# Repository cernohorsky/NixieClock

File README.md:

# NixieClock Arduino Mega shield
NixieClock PCB for nixie tubes ZM1080, ZM1082, Z570M, Z5700M. High voltage DC-DC convertor. RTC for time synchronization.

<b>Ideas:</b><br>
Different DCDC convertor parts values<br>
Different buttons position<br>

#ZM1080, #ZM1082, #Z570M, #Z5700M #Arduino, #Mega2560 #nixieclock, #nixie

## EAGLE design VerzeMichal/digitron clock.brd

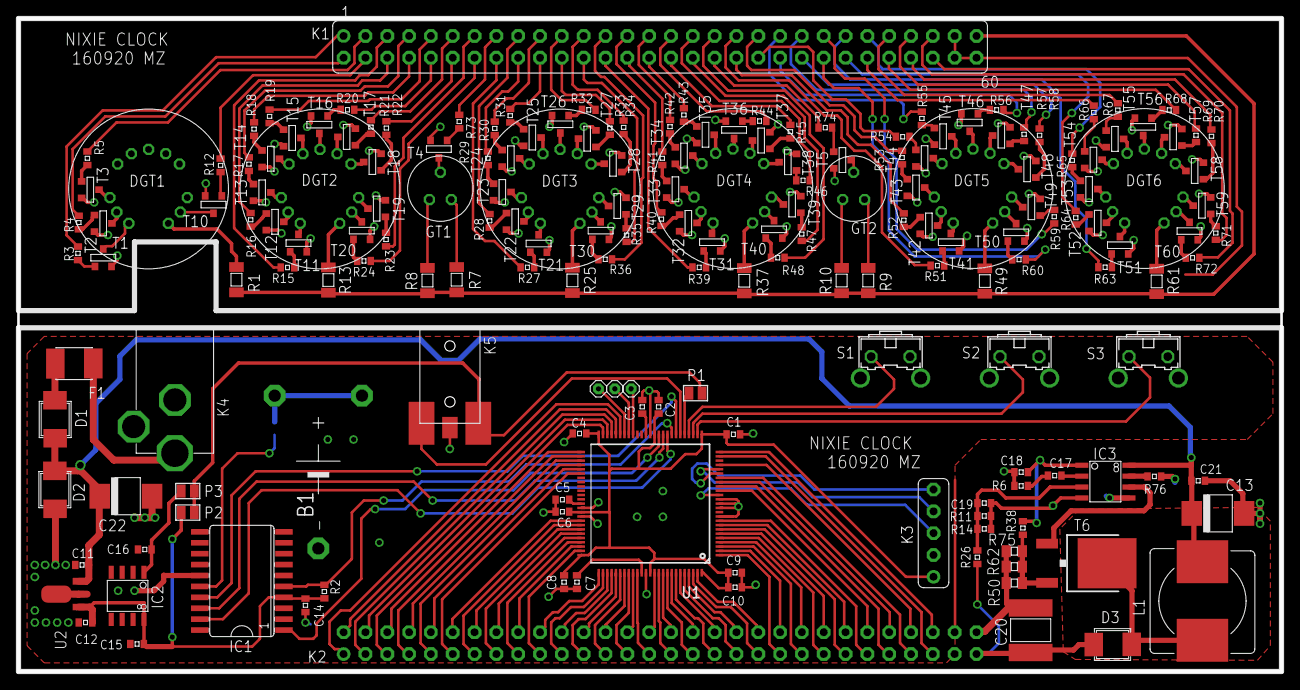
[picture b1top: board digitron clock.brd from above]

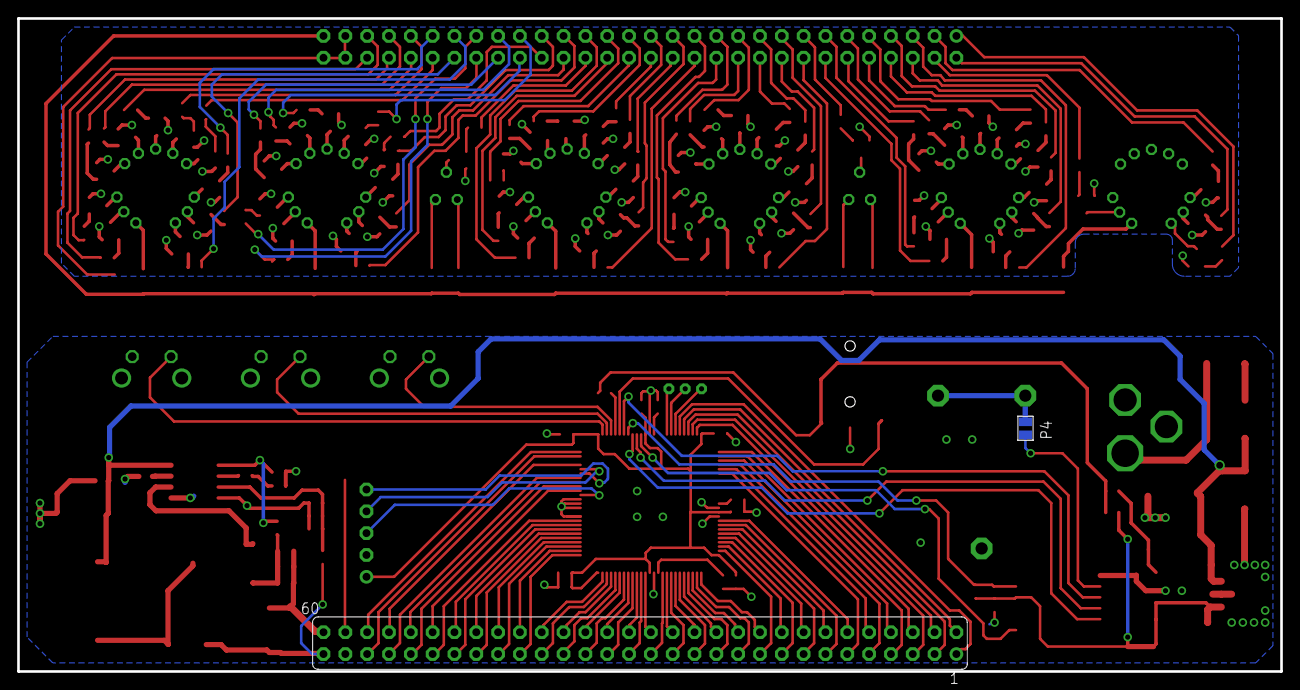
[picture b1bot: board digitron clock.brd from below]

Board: 2 copper layers, 147.0 x 76.0 mm, 189 parts (2 on the bottom side), 274 nets.

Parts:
B1: CR2430X
C1, C2, C3, C4, C5, C6, C7, C8, C9, C10, C11, C12, C14, C15, C16, C17, C18, C19, C21: 0603
C13, C22: C-D
C20: 2220
D1, D2, D3: D-SMB
DGT1, DGT2, DGT3, DGT4, DGT5, DGT6: Z570M
F1: RESETTABLE_FUSE; SMD1812
GT1, GT2: DVOJTECKA
IC1: DS3234; SO20L
IC2: LE33CD; SO8
IC3: LM3478; SO8
K1, K2: K_60PIN_F; FE30-2
K3: MA5-1
K4: DC_CONNECTOR_RAPC712; DC_CONECTOR_RAPC712
K5: JACK
K6, K7, K8: FUTURE_PAD
L1: DR127
P1, P2, P3, P4: K_SMD_PROPOJKA; JUMP-2
R1, R13, R25, R37, R49, R61: 27K; 1206
R2, R3, R4, R5, R6, R11, R12, R14, R15, R16, R17, R18, R19, R20, R21, R22, R23, R24, R26, R27, R28, R29, R30, R31, R32, R33, R34, R35, R36, R38, R39, R40, R41, R42, R43, R44, R45, R46, R47, R48, R51, R52, R53, R54, R55, R56, R57, R58, R59, R60, R63, R64, R65, R66, R67, R68, R69, R70, R71, R72, R73, R74, R76: 0603
R7, R8, R9, R10: 1M; 1206
R50, R62, R75: 0805
S1, S2, S3: B3F-31XX
T1, T2, T3, T4, T5, T10, T11, T12, T13, T14, T15, T16, T17, T18, T19, T20, T21, T22, T23, T24, T25, T26, T27, T28, T29, T30, T31, T32, T33, T34, T35, T36, T37, T38, T39, T40, T41, T42, T43, T44, T45, T46, T47, T48, T49, T50, T51, T52, T53, T54, T55, T56, T57, T58, T59, T60: SOT-23
T6: POWER_MOSFET; TO252
U1: CY8C5XXX-100PIN; TQFP-14X14-100
U2: SOT89

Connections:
+3V3: C16.1, IC2.1, P3.1
+5V: C1.1, C2.1, C4.1, C6.1, C7.1, C9.2, C10.2, K3.1, U1.26, U1.37, U1.50, U1.65, U1.75, U1.88, U1.100
+5VP: C12.2, C14.1, C15.1, IC1.4, IC2.8, P2.1, R2.2, U2.1
+12V: C11.2, C13.+, C21.1, C22.+, D1.K, D2.K, IC3.8, L1.P$2, U2.3
A0: K1.4, R12.1
A0P: K2.4, U1.48
A1: K1.1, R3.1
A1P: K2.1, U1.45
A2: K1.2, R4.1
A2P: K2.2, U1.46
A3: K1.3, R5.1
A3P: K2.3, U1.47
B0: K1.14, R24.1
B0P: K2.14, U1.69
B1: K1.5, R15.1
B1P: K2.5, U1.49
B2: K1.6, R16.1
B2P: K2.6, U1.51
B3: K1.7, R17.1
B3P: K2.7, U1.52
B4: K1.8, R18.1
B4P: K2.8, U1.53
B5: K1.9, R19.1
B5P: K2.9, U1.54
B6: K1.10, R20.1
B6P: K2.10, U1.55
B7: K1.11, R21.1
B7P: K2.11, U1.56
B8: K1.12, R22.1
B8P: K2.12, U1.67
B9: K1.13, R23.1
B9P: K2.13, U1.68
C0: K1.25, R36.1
C0P: K2.25, U1.81
C1: K1.16, R27.1
C1P: K2.16, U1.71
C2: K1.17, R28.1
C2P: K2.17, U1.72
C3: K1.18, R29.1
C3P: K2.18, U1.73
C4: K1.19, R30.1
C4P: K2.19, U1.74
C5: K1.20, R31.1
C5P: K2.20, U1.76
C6: K1.21, R32.1
C6P: K2.21, U1.77
C7: K1.22, R33.1
C7P: K2.22, U1.78
C8: K1.23, R34.1
C8P: K2.23, U1.79
C9: K1.24, R35.1
C9P: K2.24, U1.80
CLK: K3.4, U1.21
CS: IC1.1, U1.36
D0: K1.35, R48.1
D0P: K2.35, U1.94
D1: K1.26, R39.1
D1P: K2.26, U1.82
D2: K1.27, R40.1
D2P: K2.27, U1.83
D3: K1.28, R41.1
D3P: K2.28, U1.84
D4: K1.29, R42.1
D4P: K2.29, U1.85
D5: K1.30, R43.1
D5P: K2.30, U1.89
D6: K1.31, R44.1
D6P: K2.31, U1.90
D7: K1.32, R45.1
D7P: K2.32, U1.91
D8: K1.33, R46.1
D8P: K2.33, U1.92
D9: K1.34, R47.1
D9P: K2.34, U1.93
DEC1: K1.15, R73.1
DEC1P: K2.15, U1.70
DEC2: K1.36, R74.1
DEC2P: K2.36, U1.95
E0: K1.46, R60.1
E0P: K2.46, U1.6
E1: K1.37, R51.1
E1P: K2.37, U1.96
E2: K1.38, R52.1
E2P: K2.38, U1.97
E3: K1.39, R53.1
E3P: K2.39, U1.98
E4: K1.40, R54.1
E4P: K2.40, U1.99
E5: K1.41, R55.1
E5P: K2.41, U1.1
E6: K1.42, R56.1
E6P: K2.42, U1.2
E7: K1.43, R57.1
E7P: K2.43, U1.3
E8: K1.44, R58.1
E8P: K2.44, U1.4
E9: K1.45, R59.1
E9P: K2.45, U1.5
F0: K1.56, R72.1
F0P: K2.56, U1.25
F1: K1.47, R63.1
F1P: K2.47, U1.7
F2: K1.48, R64.1
F2P: K2.48, U1.8
F3: K1.49, R65.1
F3P: K2.49, U1.9
F4: K1.50, R66.1
F4P: K2.50, U1.16
F5: K1.51, R67.1
F5P: K2.51, U1.17
F6: K1.52, R68.1
F6P: K2.52, U1.18
F7: K1.53, R69.1
F7P: K2.53, U1.19
F8: K1.54, R70.1
F8P: K2.54, U1.22
F9: K1.55, R71.1
F9P: K2.55, U1.24
GND: K1.57, K1.58, K1.60, T1.2, T2.2, T3.2, T4.2, T5.2, T10.2, T11.2, T12.2, T13.2, T14.2, T15.2, T16.2, T17.2, T18.2, T19.2, T20.2, T21.2, T22.2, T23.2, T24.2, T25.2, T26.2, T27.2, T28.2, T29.2, T30.2, T31.2, T32.2, T33.2, T34.2, T35.2, T36.2, T37.2, T38.2, T39.2, T40.2, T41.2, T42.2, T43.2, T44.2, T45.2, T46.2, T47.2, T48.2, T49.2, T50.2, T51.2, T52.2, T53.2, T54.2, T55.2, T56.2, T57.2, T58.2, T59.2, T60.2
GND2: B1.-, C1.2, C2.2, C3.2, C4.2, C5.2, C6.2, C7.2, C8.1, C9.1, C10.1, C11.1, C12.1, C13.-, C14.2, C15.2, C16.2, C18.1, C19.2, C20.2, C21.2, C22.-, D2.A, IC1.15, IC2.2, IC2.3, IC2.5, IC2.6, IC2.7, IC3.4, IC3.5, K2.57, K2.58, K2.60, K3.2, K4.-, K5.GND_RS232, R6.1, R11.1, R14.1, R50.1, R62.1, R75.1, R76.1, S1.1, S2.1, S3.1, U1.10, U1.12, U1.13, U1.14, U1.38, U1.64, U1.66, U1.87, U2.2, U2.4
INT_1S: IC1.5, R2.1, U1.33
MISO: IC1.19, U1.34
MOSI: IC1.17, U1.32
unnamed: DGT1.K1, T1.3
unnamed: DGT1.K2, T2.3
unnamed: DGT1.K3, T3.3
unnamed: GT1.A1, R7.1
unnamed: GT1.A2, R8.1
unnamed: GT2.A1, R9.1
unnamed: GT1.K, T4.3
unnamed: GT2.K, T5.3
unnamed: R74.2, T5.1
unnamed: DGT1.K0, T10.3
unnamed: GT2.A2, R10.1
unnamed: DGT1.A, R1.1
unnamed: R3.2, T1.1
unnamed: R4.2, T2.1
unnamed: R5.2, T3.1
unnamed: R73.2, T4.1
unnamed: F1.A, K4.+
unnamed: D1.A, F1.K
unnamed: C3.1, U1.39
unnamed: K5.TX_RS232, P1.2, P2.2, P3.2
unnamed: R12.2, T10.1
unnamed: DGT2.K1, T11.3
unnamed: DGT2.K2, T12.3
unnamed: DGT2.K3, T13.3
unnamed: DGT2.K4, T14.3
unnamed: DGT2.K5, T15.3
unnamed: DGT2.K6, T16.3
unnamed: DGT2.K7, T17.3
unnamed: DGT2.K8, T18.3
unnamed: DGT2.K9, T19.3
unnamed: DGT2.K0, T20.3
unnamed: C5.1, U1.63
unnamed: DGT2.A, R13.1
unnamed: R15.2, T11.1
unnamed: R16.2, T12.1
unnamed: R17.2, T13.1
unnamed: R18.2, T14.1
unnamed: R19.2, T15.1
unnamed: R20.2, T16.1
unnamed: R21.2, T17.1
unnamed: R22.2, T18.1
unnamed: R23.2, T19.1
unnamed: R24.2, T20.1
unnamed: DGT3.K1, T21.3
unnamed: DGT3.K2, T22.3
unnamed: DGT3.K3, T23.3
unnamed: DGT3.K4, T24.3
unnamed: DGT3.K5, T25.3
unnamed: DGT3.K6, T26.3
unnamed: DGT3.K7, T27.3
unnamed: DGT3.K8, T28.3
unnamed: DGT3.K9, T29.3
unnamed: DGT3.K0, T30.3
unnamed: K6.1, U1.42
unnamed: DGT3.A, R25.1
unnamed: R27.2, T21.1
unnamed: R28.2, T22.1
unnamed: R29.2, T23.1
unnamed: R30.2, T24.1
unnamed: R31.2, T25.1
unnamed: R32.2, T26.1
unnamed: R33.2, T27.1
unnamed: R34.2, T28.1
unnamed: R35.2, T29.1
unnamed: R36.2, T30.1
unnamed: DGT4.K1, T31.3
unnamed: DGT4.K2, T32.3
unnamed: DGT4.K3, T33.3
unnamed: DGT4.K4, T34.3
unnamed: DGT4.K5, T35.3
unnamed: DGT4.K6, T36.3
unnamed: DGT4.K7, T37.3
unnamed: DGT4.K8, T38.3
unnamed: DGT4.K9, T39.3
unnamed: DGT4.K0, T40.3
unnamed: C17.2, IC3.2
unnamed: DGT4.A, R37.1
unnamed: R39.2, T31.1
unnamed: R40.2, T32.1
unnamed: R41.2, T33.1
unnamed: R42.2, T34.1
unnamed: R43.2, T35.1
unnamed: R44.2, T36.1
unnamed: R45.2, T37.1
unnamed: R46.2, T38.1
unnamed: R47.2, T39.1
unnamed: R48.2, T40.1
unnamed: DGT5.K1, T41.3
unnamed: DGT5.K2, T42.3
unnamed: DGT5.K3, T43.3
unnamed: DGT5.K4, T44.3
unnamed: DGT5.K5, T45.3
unnamed: DGT5.K6, T46.3
unnamed: DGT5.K7, T47.3
unnamed: DGT5.K8, T48.3
unnamed: DGT5.K9, T49.3
unnamed: DGT5.K0, T50.3
unnamed: C8.2, U1.86
unnamed: DGT5.A, R49.1
unnamed: R51.2, T41.1
unnamed: R52.2, T42.1
unnamed: R53.2, T43.1
unnamed: R54.2, T44.1
unnamed: R55.2, T45.1
unnamed: R56.2, T46.1
unnamed: R57.2, T47.1
unnamed: R58.2, T48.1
unnamed: R59.2, T49.1
unnamed: R60.2, T50.1
unnamed: DGT6.K1, T51.3
unnamed: DGT6.K2, T52.3
unnamed: DGT6.K3, T53.3
unnamed: DGT6.K4, T54.3
unnamed: DGT6.K5, T55.3
unnamed: DGT6.K6, T56.3
unnamed: DGT6.K7, T57.3
unnamed: DGT6.K8, T58.3
unnamed: DGT6.K9, T59.3
unnamed: DGT6.K0, T60.3
unnamed: C17.1, R6.2
unnamed: DGT6.A, R61.1
unnamed: R63.2, T51.1
unnamed: R64.2, T52.1
unnamed: R65.2, T53.1
unnamed: R66.2, T54.1
unnamed: R67.2, T55.1
unnamed: R68.2, T56.1
unnamed: R69.2, T57.1
unnamed: R70.2, T58.1
unnamed: R71.2, T59.1
unnamed: R72.2, T60.1
unnamed: B1.+, B1.+@1, P4.1
unnamed: C19.1, IC3.3, R11.2, R14.2, R26.2
unnamed: K7.1, U1.43
unnamed: IC3.6, T6.1
unnamed: R38.1, R50.2, R62.2, R75.2, T6.2
unnamed: K8.1, U1.44
unnamed: C18.2, IC3.1, R38.2
unnamed: IC3.7, R76.2
unnamed: D3.A, L1.P$1, T6.3
unnamed: IC1.16, P4.2
RX: K5.RX_RS232, U1.31
SCLK: IC1.18, U1.35
SDIO: K3.5, U1.20
TL1: S1.2, U1.29
TL2: S2.2, U1.28
TL3: S3.2, U1.27
TX: P1.1, U1.30
U_ANODE: K1.59, R1.2, R7.2, R8.2, R9.2, R10.2, R13.2, R25.2, R37.2, R49.2, R61.2
U_ANODEP: C20.1, D3.K, K2.59, R26.1
XRES: K3.3, U1.15

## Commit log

2019-03-14 Final v1.0
2019-03-19 BJT transistors test. added Arduino Mega dimensions
2019-03-19 Added Arduino Mega dimensions, Added DS3231
2019-03-20 Added pin headers for Arduino Mega. Added first two nixies, Changed PCB dimensions
2019-03-20 Added all nixies, added DC-DC converter, basic routing done
2019-03-20 Routing finished v0.1
2019-03-21 Added RTC, ERC done, DRC done, Silk layer revision
2019-03-22 Added KiCAD lib files
2019-03-22 Deleted old gerber files
2019-03-22 Added buttons
2019-03-22 PCB manufactured
2019-03-22 Small changes
2019-04-06 DC-DC convertor updatet values
2019-04-16 Firmware - Nixies testing
2019-04-17 GPIOs correction, Added RTC reading (first test)
2019-04-18 First version of working firmware. Small components values change
2019-04-18 Changed BJT base resistor values, Added photo, Added new inspiration schematic, Changed README
2019-04-23 Solved I2C, UART conflict
2019-04-24 Added - Turn off during night function
2019-05-07 Faster RTC initialization
